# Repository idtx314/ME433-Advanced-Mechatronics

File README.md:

# ME433-Advanced-Mechatronics
HW and project repository for Advanced Mechatronics Class
This repository contains various sub-projects building up to the creation of a line following drone control program.

Note to self: To better test the filters, since they're digital, just run different variations of the same one on the same data simultaneously and graph the results

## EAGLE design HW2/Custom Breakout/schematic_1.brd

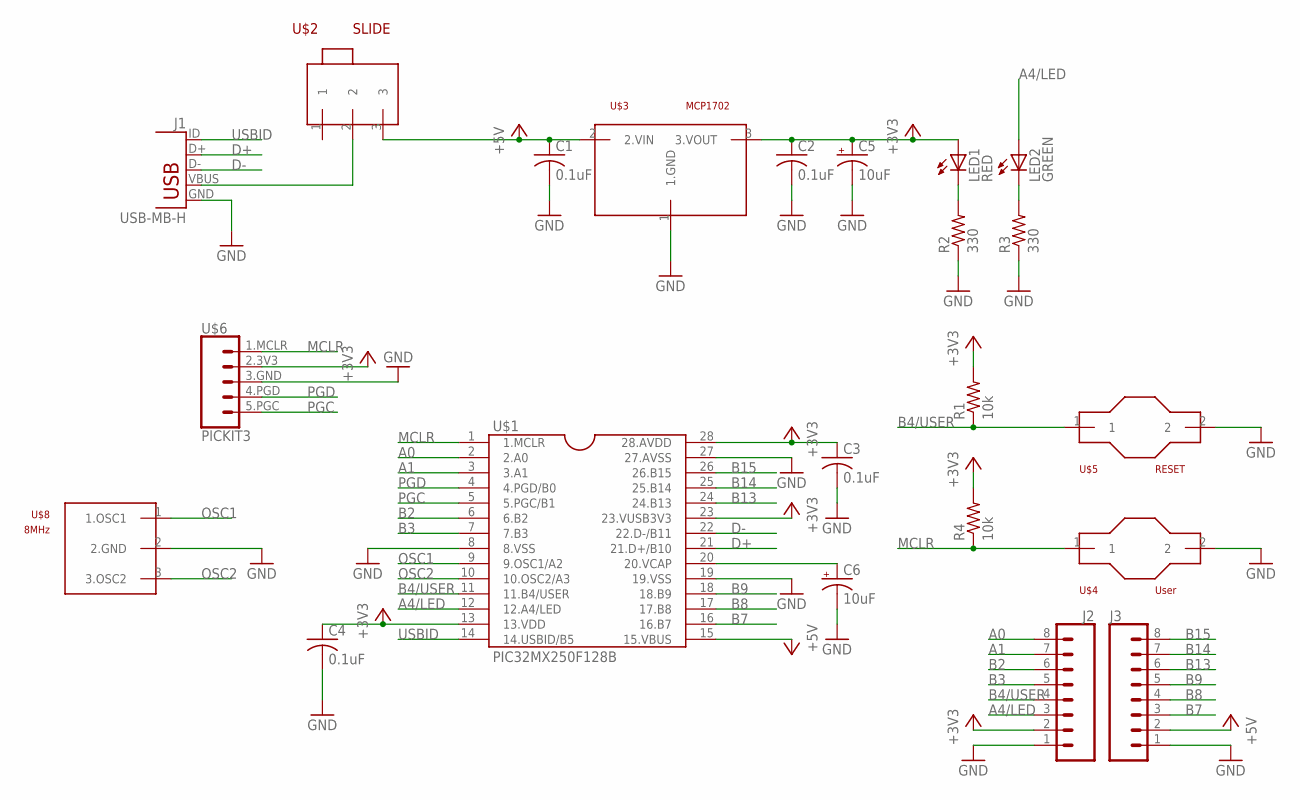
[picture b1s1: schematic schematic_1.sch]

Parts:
C1, C2, C3, C4: 0.1uF; C025-025X050
C5, C6: 10uF; B45181B
J1: USB-MB-H
J2, J3: CONN_08"; 1X08
LED1: RED; LED3MM
LED2: GREEN; LED3MM
R1, R4: 10k; 0207/10
R2, R3: 330; 0207/10
U$1: PIC32MX250F128B; DIL28-3
U$2: SLIDE
U$3: MCP1702; TO92
U$4: User; BUTTON
U$5: RESET; BUTTON
U$6: PICKIT3
U$8: 8MHz; OSC

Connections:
+3V3: C2.1, C3.1, C4.1, C5.+, J2.2, LED1.A, R1.2, R4.2, U$1.13 (13.VDD), U$1.23 (23.VUSB3V3), U$1.28 (28.AVDD), U$3.3 (3.VOUT), U$6.2.3V3 (2.VDD)
+5V: C1.1, J3.2, U$1.15 (15.VBUS), U$2.3, U$3.2 (2.VIN)
A0: J2.8, U$1.2 (2.A0)
A1: J2.7, U$1.3 (3.A1)
A4/LED: J2.3, LED2.A, U$1.12 (12.A4/LED)
B2: J2.6, U$1.6 (6.B2)
B3: J2.5, U$1.7 (7.B3)
B4/USER: J2.4, R1.1, U$1.11 (11.B4/USER), U$5.1
B7: J3.3, U$1.16 (16.B7)
B8: J3.4, U$1.17 (17.B8)
B9: J3.5, U$1.18 (18.B9)
B13: J3.6, U$1.24 (24.B13)
B14: J3.7, U$1.25 (25.B14)
B15: J3.8, U$1.26 (26.B15)
D+: J1.D+, U$1.21 (21.D+/B10)
D-: J1.D-, U$1.22 (22.D-/B11)
GND: C1.2, C2.2, C3.2, C4.2, C5.-, C6.-, J1.GND, J2.1, J3.1, R2.1, R3.1, U$1.8 (8.VSS), U$1.19 (19.VSS), U$1.27 (27.AVSS), U$3.1 (1.GND), U$4.2, U$5.2, U$6.3.GND, U$8.2 (2.GND)
MCLR: R4.1, U$1.1 (1.MCLR), U$4.1, U$6.1.MCLR
unnamed: LED2.K (C), R3.2
unnamed: J1.VBUS, U$2.2
unnamed: C6.+, U$1.20 (20.VCAP)
unnamed: LED1.K (C), R2.2
OSC1: U$1.9 (9.OSC1/A2), U$8.1 (1.OSC1)
OSC2: U$1.10 (10.OSC2/A3), U$8.3 (3.OSC2)
PGC: U$1.5 (5.PGC/B1), U$6.5.PGC
PGD: U$1.4 (4.PGD/B0), U$6.4.PGD
USBID: J1.ID, U$1.14 (14.USBID/B5)

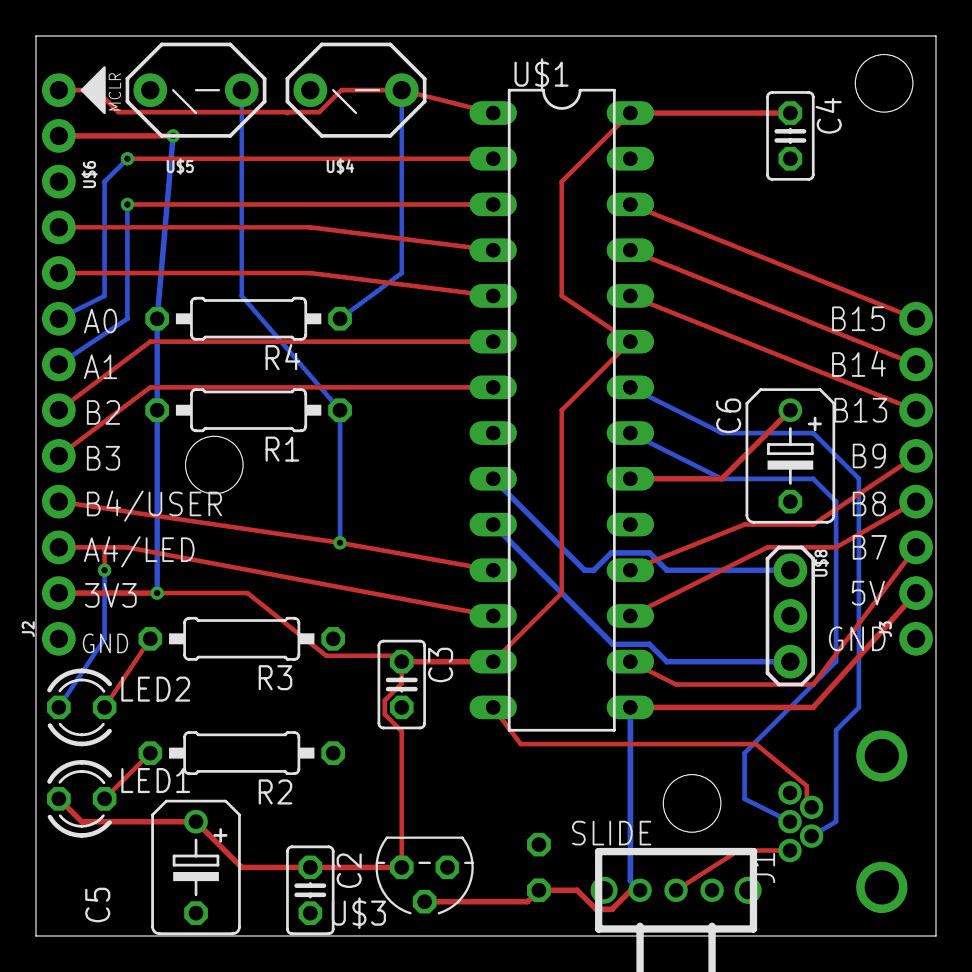
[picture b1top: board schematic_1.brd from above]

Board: 2 copper layers, 50.0 x 50.0 mm, 22 parts (1 on the bottom side), 27 nets.

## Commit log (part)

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2018-04-05 Initial Commit. Reference material collected into a directory.
2018-04-05 Decided to track reference material as parts of specific HW assignments. Trying to remove file from cache.
2018-04-05 Testing git rm .
2018-04-10 Added .1uF capacitors from input to ground, then output to ground of the voltage regulator. Second capacitor removed the previous oscillations.
2018-04-10 Completed the build and took a picture.
2018-04-10 Added outline code file.
2018-04-11 Made clock calculations and set pragma settings.
2018-04-11 Set the last of the pragmas and started on the blink code outline. Created a proper MPLABX project folder so that I can actually compile and load the project.
2018-04-11 Migrated all the template code to main.c in the MPLABX project.
2018-04-11 Placed LED on a square wave with period of 0.5ms, added picture to repo. Timing seems to be working.
2018-04-12 Added code to stop the blinking and leave the LED off while the user button is pressed. Tried to add a video, but that caused github to eat itself and wasted hours of my time.
2018-04-12 Completed the part and connection schematic.
2018-04-12 Created custom library to contain everything for the PCB.
2018-04-12 Created a fake smaller version of the file which I have attempted to untrack.
2018-04-12 Having some issues with getting origin resynced after it refused to accept the large video file HW1/00001.MTS, then refused to delete the large video file that it never accepted.
2018-04-12 Was able to squash the commits adding and then removing the video, thus essentially negating it from the history. used: git rebase -i HEAD~10 where 10 was the number of commits to go back in history 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
2018-04-13 Did most of the work for the .brd layout. Still have a few minor issues on the to do list before I generate gerber files.
2018-04-14 Added a graphic, improved the screw holes, various tweaking. I've got some leftover nonsensical issues to figure out. Right now I'm trying to get the cam file downloaded. May just have to clone the e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
2018-04-16 Final adjustments, moved the new gerber files into the HW directory. Never figured out why some of the silkscreen for the parts shows up on the bottom. Ignoring that for now.
2018-04-22 Found formula for DAC output voltage, correct calculation in setVoltage().
2018-04-22 I've programmed and wired what should be a working SPI module. I'v validated the clock coming out of the PIC, the CS signal spikes at reasonable intervals, although I note the spikes aren't very dist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
2018-04-23 Changed SPI1BRG from 0x1 to 0x3999, added a third byte to the voltage transmission, and set the don't care bits in the message struct explicitly. Going to try building a message manually.
2018-04-23 Experimenting with unions reveals that the bit fields are arranged in order from least to most significant, where I had been assuming the opposite. Rearranging the fields in my union has produced sig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
2018-04-23 Reverted debug changes and validated the setup to produce a 1ms square wave on channel b.
2018-04-23 Prototyped waveform generator functions in python, where it's easy to plot them. Converted those functions to C and integrated them into the codebase. Main calls demo_wave(), which sets the vout chan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
2018-04-23 Put the files in the wrong place last commit. Woops.
2018-04-23 Added two photos of the circuit and its schematic.
2018-04-24 Added notes to HW4.
2018-04-27 Created HW5 by copying HW4. I have added the given i2c library to the project files and done I2C initiation on the PIC, including turning off the default analog functions of the I2C2 pins. I will nex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
2018-04-28 Setup function for I2C on channel 2 complete and validated, I2C port expander set up and validated with an LED on channel GP0. Now testing expander read and write. Added i2c_init_expander().
2018-04-28 Picture added. Video stored in Reference file (untracked).
2018-04-30 Copied HW5 code into HW6. This new assignment will take over the SPI ports that were used for the DAC chip. Ostensibly we won't be using that anymore.
2018-04-30 Added new libraries for SPI1 and LCD to HW6. Deleted older functions related to SPI tasks.
2018-05-01 Added functions to write a character, a string, and a progress bar as described in the HW6 assignment. Wrapping this assignment and turning it in. The LCD is behaving better for the moment, but I don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
2018-05-01 Added HW7 project, for getting the IMU up and running. Troubleshooting the LCD power issue, I'm finding it difficult to reproduce. I suspect that the wiring for the MCLR may be involved in some way. 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
2018-05-01 Added a Timer 4 interrupt to control the heartbeat. Shouldn't have to worry about moving it around anymore.
2018-05-02 Added a picture for HW7. Wrote IMU configuration and reading functions in the i2clib.c file. Trying to get everything working and tested now.
2018-05-03 Ended up being that I hadn't initiated I2C. I've resolved most of the issues, but I'm getting some weirdness with my accelerometer axes. The sign of the output is the opposite of what it should be on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
2018-05-03 Completed the bar code and made a video to turn in.
2018-05-04 Added a new HW8 folder, containing a harmony project version of HW1+HW8. The HW is running normally on my PIC. Had to abandon the interrupt based heartbeat for now, I'm not sure how to port it over t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
2018-05-06 Added new file for HW9. I've created the HW9 project and followed the setup instructions to get the template code running, but the microcontroller is not opening a port.
2018-05-09 Moved LCD functions for HW7 into the LCD library and tested that they were still working by commenting them out and rerunning HW7.
2018-05-09 Removed the now unneeded functions and prototypes from HW7 main.c
2018-05-09 Added I2C init to HW9. Added some missing header prototypes to HW7 and moved the imu test code into a separate function. I'll next port that over to the HW9 code.
2018-05-09 Moved the imu_test() function into the i2c header as well and tested that it was working with HW7. Ported it into the HW9 library and successfully tested it in the looping USB code. Also noted that t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
2018-05-09 Got the i2c_read_imu(float*) function working. This takes a 7 float array, reads and converts imu data, and stores that data in the array. Tested this with HW7 code. Now porting to HW9.
2018-05-09 Z axis accelerometer data is transmitting to screen at 5Hz. Now adjusting to 100Hz.
2018-05-09 Z axis accel data transmitting at 100Hz. Now setting it up to read at 5Hz while still transmitting at 100Hz. Not clear on why this was assigned.
2018-05-09 I think it's now reading at 5 and transmitting at 100, but it's a bit hard to tell.
2018-05-10 The program is functioning mostly as it's supposed to, but it's definitely far slower than it should be. Should ask Nick and others about that.
2018-05-10 Removed global variable i. I think the LCD could be part of the speed issue.
2018-05-10 Also changed the IMU read to 100Hz like the rest of the loop and removed the readTime variable. Nick says that he wanted us to read as well as transmit at 100Hz.
2018-05-16 Added HW10, copied HW9 code into HW10 folder (partially validated copy). Modified code to apply 3 filters to z axis data and read out results, but I seem to only be recording the most recent reading 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
2018-05-16 Found the logic error, I was setting the buffer array to zeros each time through the loop instead of just the first. Added some weights for a length 4 FIR filter.
2018-05-17 Note about filter validation in readme.
2018-05-17 Added HW 11 and went through the step by step guide. It's a very short leap from there to having the mouse working, I'm now putting the finishing touches on it.
2018-05-17 Added the chart for HW10. Got HW11 to a good sensitivity.
2018-05-25 Began working on HW 13, to use the android camera to find green objects. I've copied the code from the repo and with Aamir's help identified the areas to target for editing. Code is currently finding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
2018-05-25 I have added a slider to adjust the sensitivity and the code is highlighting only green things, rather than green and blue.
2018-06-03 Can now receive and send back numbers through screen, as described in wiki writeup.
2018-06-03 May have forgotten to add the android part of the repo.
2018-06-03 Added a pre-compiled USB library.
2018-06-05 Added pictures and CAD files to HW15 directory.
2018-06-05 Added screenshots of the CAD files.
2018-06-07 Started on HW16, creating a PI controller for motor velocity. I have a skeleton up that should approximate the final program and have filled in most of the interrupt.
2018-06-13 Accidentally duplicated PImain.c, the prototype motor control code. Deleting the extra and leaving the prototype in the HW16 directory.
2018-06-14 HW16 code is tested to the extent that it causes the motors to move. I will need to make a couple of wiring adjustments, but assembly of the first prototype has gone pretty well. Added a video of the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
2018-06-14 Created HW17 by copying and slightly modifying HW13 with new code.
2018-06-14 Added a video for HW 17 in the relevant repository. Added HW18, including a picture of the assembled chassis. Now working on code merges for HW18.
2018-06-14 Discovered that MPLABX doesn't actually copy projects properly when source code is external, which it is by default in harmony. Now starting HW18 files from scratch.
2018-06-14 HW18 code is controlling the motors (poorly), counting over USB, and echoing numbers over usb.
2018-06-14 Added a copy of the HW17 line finder project to the HW18 folder.
2018-06-14 I have cobbled together the code from HW17 and HW14 in an attempt to establish comms while operating motor control. The PIC is listening, responding, and controlling as expected. Unfortunately The an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
2018-08-23 Added a new project 'Android 2' in the HW18 directory. My first attempt at producing an android program to communicate camera data to the pic crashed whenever it was launched. This project will be my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
2018-08-25 Android 2 is tested and working with the HW14 code for the pic. This demonstrates that the USB communication channel is working between the pic and the android.
2018-08-26 HW18 PIC code is confirmed to communicate back and forth with the Android2 code copied from HW14. I don't have a way to re-charge the motor battery at this time, so I can't properly test the motor co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
2018-08-27 Modified AndroidManifest.xml as instructed in AndroidCamera.md to add permissions for the camera and lock the app orientation. This is tested and still working with the CoM calculating PIC code.
2018-08-28 Alterations to activity_main.xml to prep for new features. Tested and working with PIC.
2018-08-28 Integrated all camera code changes from HW17. The combined program now demonstrates all functionality from both the USB and the Image processing versions of the android code, and is communicating nor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
2018-08-29 Added code to automatically send the CoM whenever the phone calculates it. Tested with the PIC code and the echoes coming back are behaving as expected, setting the left and right wheel velocities ap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
2018-09-03 Uncommented a critical segment of motor control code that I had previously turned off for troubleshooting. Corrected an error that would have caused integrated velocity error to always be 500. Increa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
2018-09-03 Various troubleshooting changes. This should probably have been a branch. Switching off the I component of the controller removes the stuttering issue. Using a lower Ki helps, but results in signific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
2018-10-11 After examining the intermediate values going through the velocity controller I concluded that the encoder is being read much too frequently for its resolution/the wheel speeds. This is resulting the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
2018-10-11 Prototype moving average velocity filter added to project code.
